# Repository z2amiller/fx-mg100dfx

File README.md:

# fx-mg100dfx

## MG100DFX Distortion (OD1/OD2)

A pedal port of the overdrive channel from the Marshall MG100DFX solid-state
amp, built for a [PedalPCB forum request][post]. The +/-15V bipolar original is
re-biased for single-supply operation.

### The circuit

Input stage (x11 non-inverting) into a high-gain summing stage that clips into
an antiparallel red/green LED pair across its feedback — even quiet playing
comes out almost as a square wave. The OD1/OD2 switch adds two extra input
branches (more gain, fuller voicing). Marshall-style treble/bass/middle stack,
contour, volume, then a x11 recovery stage.

### Power and headroom

- 9V: fully functional but not completely true to the original tone. The input stage rail-clips hot transients (above roughly 350mV peaks) before the LED clipper.
- 18V: reproduces the original amp's front-end dynamics essentially exactly (sim-verified: identical stage-1 swing to the +/-15V original). Electrolytics are 25V-rated for this.

### No-cap-mult (purist) build

Aggressive power rail filtering is done through a capacitor multiplier at the voltage input. This drops ~1V total between the reverse polarity protection diode and the capacitor multiplier.

If you have a clean supply and want to recover some of the headroom, you can
omit Q1 jumper Q1 pads 2-3 (B and E on the BC547 footprint), and fit 47R at
R23 (Just above the 4-pin connector at the south of the board) instead of 10k.
you get a plain RC filter (47R into ~200uF) — about 34dB less ripple filtering,
about 0.5V less drop. At 18V the saved drop is meaningless — this option is
parts-count preference, not tone.

### Parts notes

- D2/D3 clipping LEDs: use old-school GaP green (Vf ~2.0-2.2V). A modern InGaN green (2.6-2.9V) hits the op-amp rail before the LED clamps at 9V and kills the intended red/green asymmetric clipping.
- Q1 is BC547C (C-B-E). If substituting 2N5088, its pinout is E-B-C — check before soldering.
- Film caps in the signal path, ceramic disc for pF values, per the BOM.
- Hybrid I/O: populate EITHER the JST-PH headers (daughterboard style) OR the PedalPCB-style wire pads (IN at the bottom edge, VIN/GND at top). The daughterboard layout that supports this is at the [pedalfx repo][repo].

[post]: https://forum.pedalpcb.com/threads/help-needed-to-design-od1-od2-pedal-from-mg100dfx-amp.27087/
[repo]: https://github.com/z2amiller/pedalfx/tree/main/template

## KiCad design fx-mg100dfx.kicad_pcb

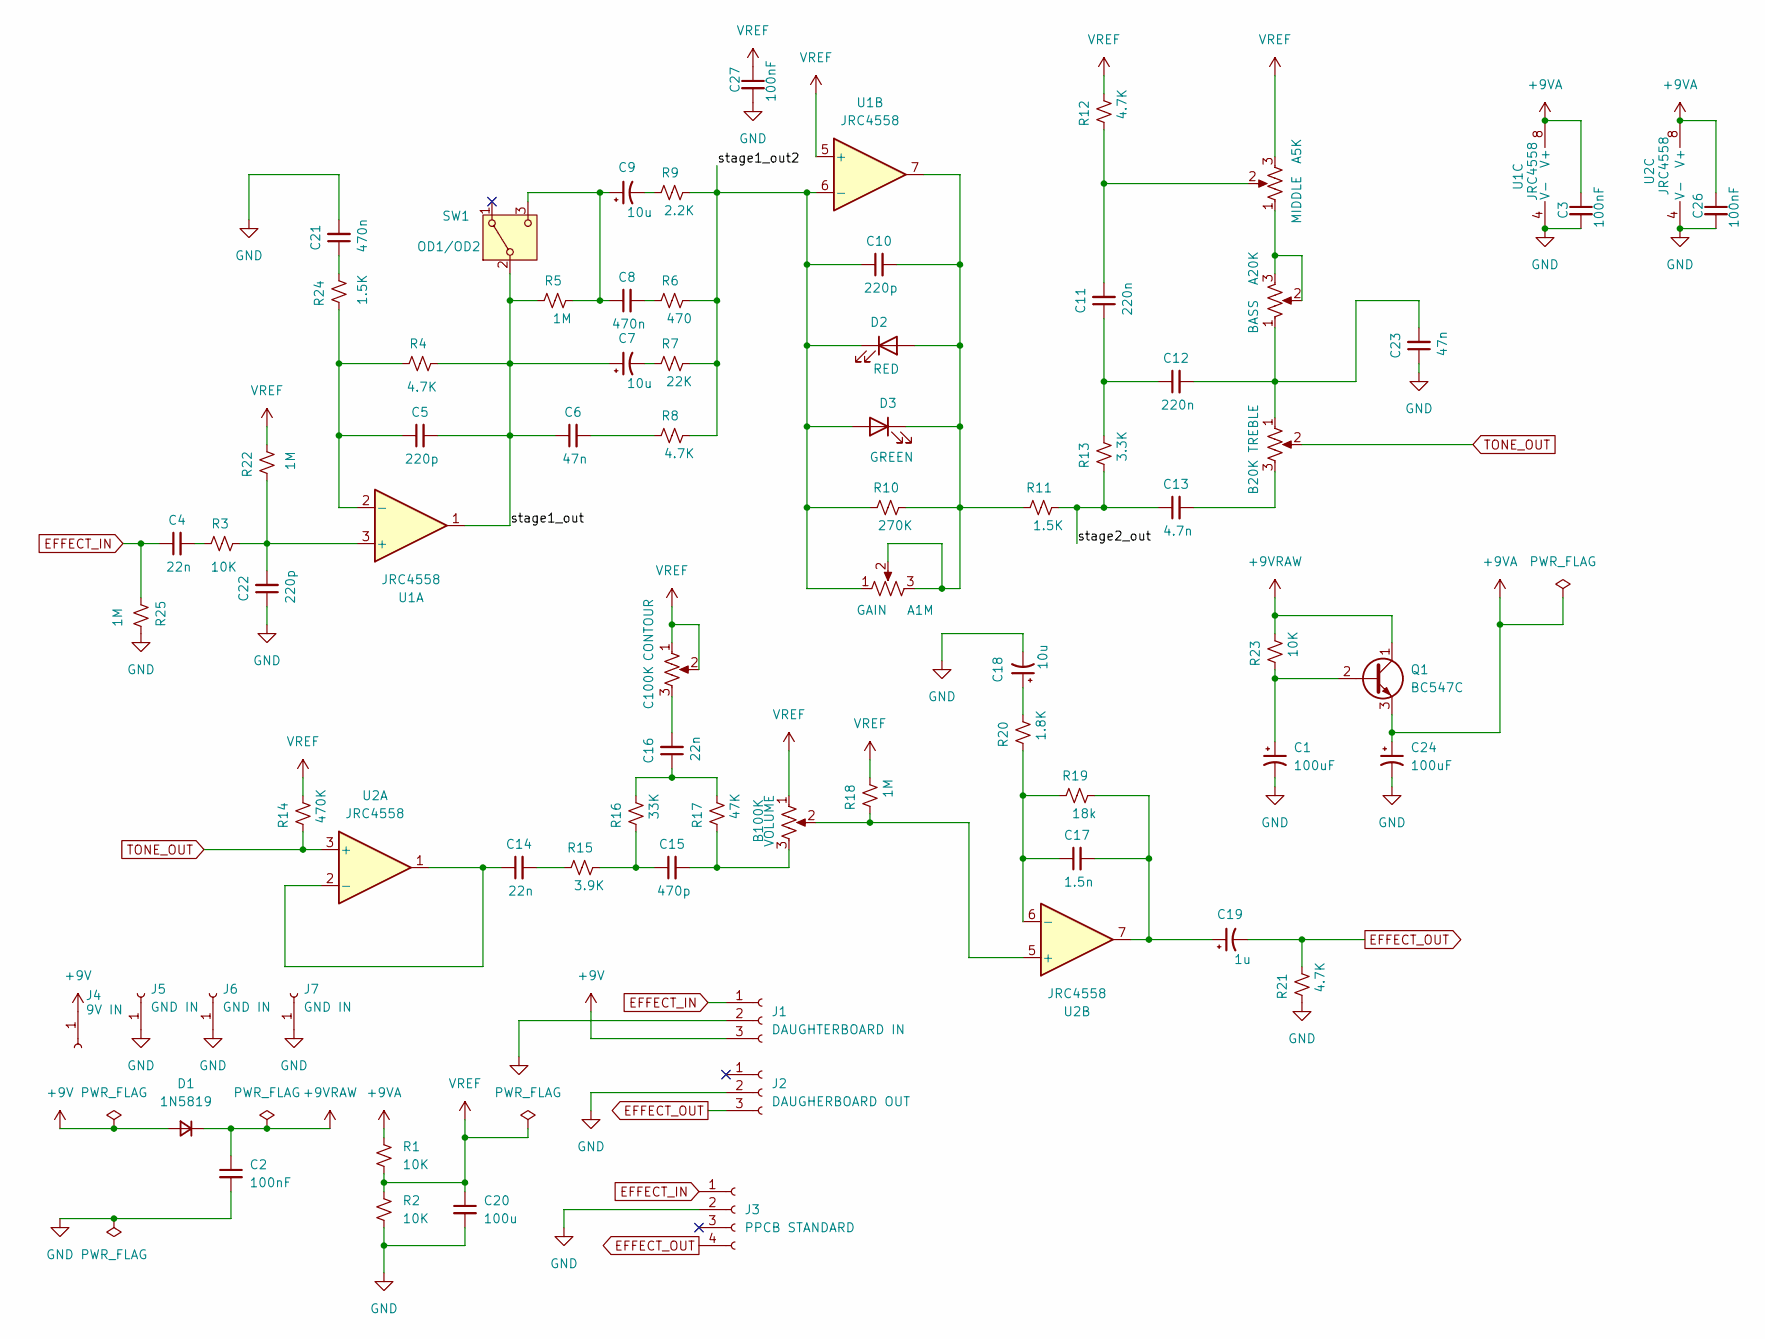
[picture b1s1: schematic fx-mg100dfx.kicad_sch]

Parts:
C1, C24: 100uF; CP_Radial_D6.3mm_P2.50mm; LCSC C88744
C2, C3, C26, C27: 100nF; C_Disc_D3.4mm_W2.1mm_P2.50mm; LCSC C14663
C4, C14, C16: 22n; C_Rect_L7.2mm_W2.5mm_P5.00mm_FKS2_FKP2_MKS2_MKP2
C5, C10, C22: 220p; C_Disc_D4.3mm_W1.9mm_P5.00mm
C6: 47n; C_Rect_L7.2mm_W2.5mm_P5.00mm_FKS2_FKP2_MKS2_MKP2
C7, C9, C18: 10u; CP_Radial_D5.0mm_P2.00mm
C8, C21: 470n; C_Rect_L7.2mm_W3.5mm_P5.00mm_FKS2_FKP2_MKS2_MKP2
C11, C12: 220n; C_Rect_L7.2mm_W3.0mm_P5.00mm_FKS2_FKP2_MKS2_MKP2
C13: 4.7n; C_Rect_L7.2mm_W2.5mm_P5.00mm_FKS2_FKP2_MKS2_MKP2
C15: 470p; C_Disc_D4.3mm_W1.9mm_P5.00mm
C17: 1.5n; C_Rect_L7.2mm_W2.5mm_P5.00mm_FKS2_FKP2_MKS2_MKP2
C19: 1u; CP_Radial_D5.0mm_P2.00mm
C20: 100u; CP_Radial_D5.0mm_P2.50mm; LCSC C14663
C23: 47n; C_Rect_L7.2mm_W3.0mm_P5.00mm_FKS2_FKP2_MKS2_MKP2
D1: 1N5819; D_DO-41_SOD81_P7.62mm_Horizontal; LCSC C191023
D2: RED; LED_D5.0mm
D3: GREEN; LED_D5.0mm
J1: DAUGHTERBOARD IN; JST_PH_B3B-PH-K_1x03_P2.00mm_Vertical; LCSC C131339
J2: DAUGHERBOARD OUT; JST_PH_B3B-PH-K_1x03_P2.00mm_Vertical; LCSC C131339
J3: PPCB STANDARD; PinHeader_1x04_P2.54mm_Vertical
J4: 9V IN; PinHeader_1x01_P2.54mm_Vertical
J5, J6, J7: GND IN; PinHeader_1x01_P2.54mm_Vertical
Q1: BC547C; TO_92_Inline_Wide
R1, R2, R3, R23: 10K; R_Axial_DIN0207_L6.3mm_D2.5mm_P7.62mm_Horizontal; LCSC C25804
R4, R8, R12, R21: 4.7K; R_Axial_DIN0207_L6.3mm_D2.5mm_P7.62mm_Horizontal; LCSC C25804
R5, R18, R22, R25: 1M; R_Axial_DIN0207_L6.3mm_D2.5mm_P7.62mm_Horizontal; LCSC C25804
R6: 470; R_Axial_DIN0207_L6.3mm_D2.5mm_P7.62mm_Horizontal; LCSC C25804
R7: 22K; R_Axial_DIN0207_L6.3mm_D2.5mm_P7.62mm_Horizontal; LCSC C25804
R9: 2.2K; R_Axial_DIN0207_L6.3mm_D2.5mm_P7.62mm_Horizontal; LCSC C25804
R10: 270K; R_Axial_DIN0207_L6.3mm_D2.5mm_P7.62mm_Horizontal; LCSC C25804
R11, R24: 1.5K; R_Axial_DIN0207_L6.3mm_D2.5mm_P7.62mm_Horizontal; LCSC C25804
R13: 3.3K; R_Axial_DIN0207_L6.3mm_D2.5mm_P7.62mm_Horizontal; LCSC C25804
R14: 470K; R_Axial_DIN0207_L6.3mm_D2.5mm_P7.62mm_Horizontal; LCSC C25804
R15: 3.9K; R_Axial_DIN0207_L6.3mm_D2.5mm_P7.62mm_Horizontal; LCSC C25804
R16: 33K; R_Axial_DIN0207_L6.3mm_D2.5mm_P7.62mm_Horizontal; LCSC C25804
R17: 47K; R_Axial_DIN0207_L6.3mm_D2.5mm_P7.62mm_Horizontal; LCSC C25804
R19: 18k; R_Axial_DIN0207_L6.3mm_D2.5mm_P7.62mm_Horizontal; LCSC C25804
R20: 1.8K; R_Axial_DIN0207_L6.3mm_D2.5mm_P7.62mm_Horizontal; LCSC C25804
RV1: A1M; 16MM_B.MOUNT
RV2: B20K; 16MM_B.MOUNT
RV3: A20K; 16MM_B.MOUNT
RV4: A5K; 16MM_B.MOUNT
RV5: C100K; 16MM_B.MOUNT
RV6: B100K; 16MM_B.MOUNT
SW1: OD1/OD2; SPDT.LUGS
U1, U2: JRC4558; DIP-8_W7.62mm_Socket

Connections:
+9V: D1.2 (A), J1.3, J4.1 (Pin_1_1)
+9VA: C3.1, C24.1, C26.1, Q1.3 (E), R1.2, U1.8 (V+), U2.8 (V+)
+9VRAW: C2.1, D1.1 (K), Q1.1 (C), R23.2
/stage1_out: C5.2, C6.1, C7.1, R4.2, R5.1, SW1.2 (B), U1.1
/stage1_out2: C10.1, D2.1 (K), D3.2 (A), R6.2, R7.2, R8.2, R9.2, R10.1, RV1.1, U1.6 (-)
/stage2_out: C13.1, R11.2, R13.1
EFFECT_IN: C4.1, J1.1, J3.1, R25.1
EFFECT_OUT: C19.2, J2.3, J3.4, R21.2
GND: C1.2, C2.2, C3.2, C18.2, C20.2, C21.2, C22.1, C23.1, C24.2, C26.2, C27.2, J1.2, J2.2, J3.2, J5.1 (Pin_1_1), J6.1 (Pin_1_1), J7.1 (Pin_1_1), R2.2, R21.1, R25.2, U1.4 (V-), U2.4 (V-)
unnamed: C4.2, R3.1
unnamed: C6.2, R8.1
unnamed: C7.2, R7.1
unnamed: C8.2, R6.1
unnamed: C9.2, R9.1
unnamed: C11.1, C12.1, R13.2
unnamed: C11.2, R12.1, RV4.2
unnamed: C12.2, C23.2, RV2.1, RV3.1
unnamed: C13.2, RV2.3
unnamed: C14.2, R15.1
unnamed: C15.1, R15.2, R16.1
unnamed: C15.2, R17.1, RV6.3
unnamed: C16.1, R16.2, R17.2
unnamed: C16.2, RV5.3
unnamed: C17.2, C19.1, R19.2, U2.7
unnamed: C18.1, R20.2
unnamed: C21.1, R24.2
unnamed: C10.2, D2.2 (A), D3.1 (K), R10.2, R11.1, RV1.2, RV1.3, U1.7
unnamed: C1.1, Q1.2 (B), R23.1
unnamed: RV3.2, RV3.3, RV4.1
unnamed: C8.1, C9.1, R5.2, SW1.3 (C)
unnamed: C22.2, R3.2, R22.1, U1.3 (+)
unnamed: C5.1, R4.1, R24.1, U1.2 (-)
unnamed: C14.1, U2.1, U2.2 (-)
unnamed: R18.1, RV6.2, U2.5 (+)
unnamed: C17.1, R19.1, R20.1, U2.6 (-)
TONE_OUT: R14.1, RV2.2, U2.3 (+)
VREF: C20.1, C27.1, R1.1, R2.1, R12.2, R14.2, R18.2, R22.2, RV4.3, RV5.1, RV5.2, RV6.1, U1.5 (+)

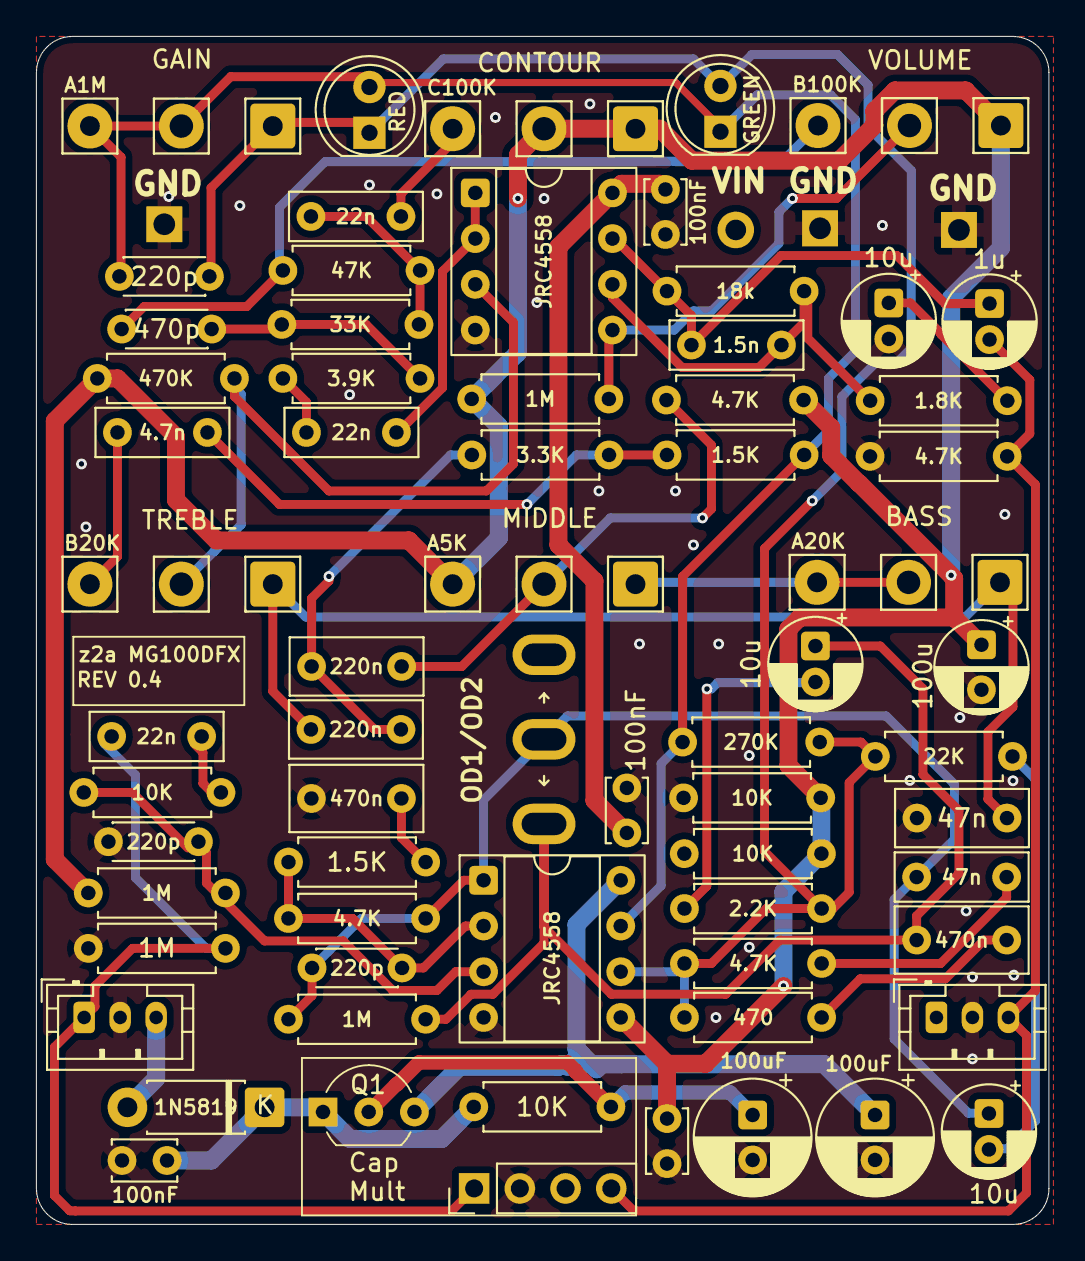
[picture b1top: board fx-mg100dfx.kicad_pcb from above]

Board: 4 copper layers, 56.2 x 66.0 mm, 71 parts (0 on the bottom side), 37 nets.
